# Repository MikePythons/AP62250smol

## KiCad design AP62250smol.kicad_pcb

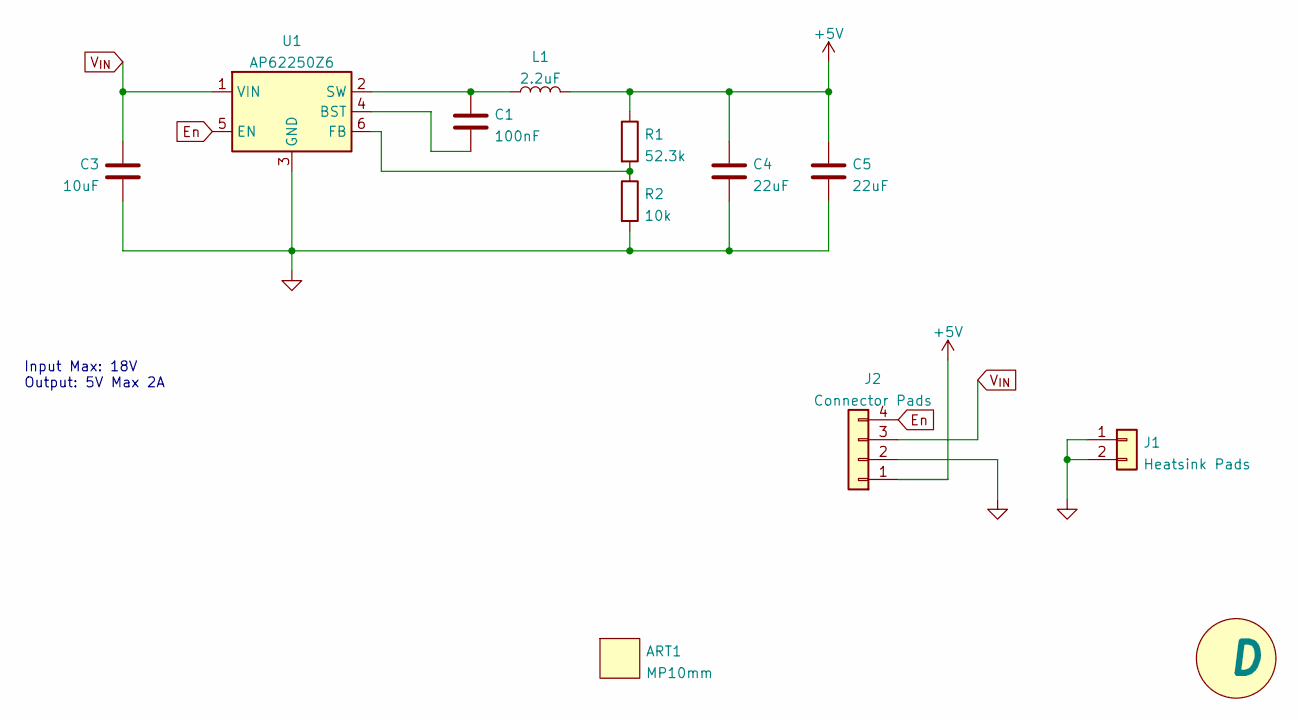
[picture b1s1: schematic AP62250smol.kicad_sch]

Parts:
ART1: MP10mm; MPSquare_10mm
C1: 100nF; C_0603_1608Metric
C3: 10uF; C_1206_3216Metric
C4, C5: 22uF; C_1206_3216Metric
J1: Heatsink Pads; Castellated_1x2_2.54mm
J2: Connector Pads; Castellated_2x4_2.54mm
L1: 2.2uF; L_Inductor_tdk_VLS5045EX
MISC1: D; RevisionSymbol_Small
R1: 52.3k; C_0603_1608Metric
R2: 10k; C_0603_1608Metric
U1: AP62250Z6; SOT-563_wider_clearance

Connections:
+5V: C4.1, C5.1, J2.1, L1.2, R1.1
En: J2.4, U1.5 (EN)
GND: C3.2, C4.2, C5.2, J1.1, J1.2, J2.2, R2.2, U1.3 (GND)
unnamed: C1.1, L1.1, U1.2 (SW)
unnamed: C1.2, U1.4 (BST)
unnamed: R1.2, R2.1, U1.6 (FB)
V_{IN}: C3.1, J2.3, U1.1 (VIN)

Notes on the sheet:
Input Max: 18V Output: 5V Max 2A

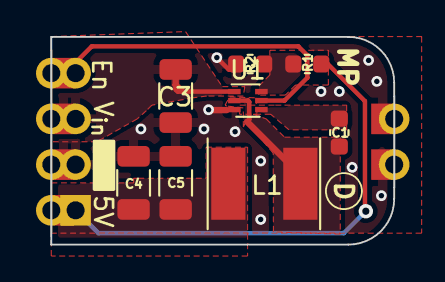
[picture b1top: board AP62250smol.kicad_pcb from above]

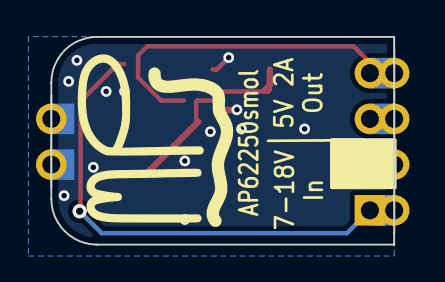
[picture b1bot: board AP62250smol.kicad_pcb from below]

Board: 2 copper layers, 19.0 x 11.5 mm, 12 parts (2 on the bottom side), 7 nets.

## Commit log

2021-12-25 Revision B upload. This is essentially just a silkscreen revision, however I moved a couple of stitching vias so I prefer to consider this a new revision just in case I angered the switching gods in 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
2021-12-27 I am a liar who lies. This is RevB. Major revision changes board dimensions and increases input capacitor to 1206
2021-12-27 Removed second input capacitor.
2021-12-27 Actually, RevC
2021-12-27 Silk Update
2022-01-23 Updated IC footprint to allow 0.2mm spacing between pads. This allows for solder mask between pads if ordering green solder mask from JLCPCB
